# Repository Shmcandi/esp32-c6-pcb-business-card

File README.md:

# ESP32-C6 Smart PCB Business Card

An ultra-slim, monolithic smart electronic business card in the standard ISO/IEC 7810 ID-1 credit card form factor ($85.6 \times 54.0\text{ mm}$), powered by an **Espressif ESP32-C6-MINI-1** with an integrated **0.91" 128×32 SPI OLED display**, onboard USB-C programming and autonomous Li-Po battery charging.

Everything is designed for direct surface-mount soldering with **zero pin headers, zero sockets, and zero through-holes** for the OLED.

---

## 📸 Photorealistic 3D Renders

| Isometric / Perspective View | Top View | Bottom View |
| :---: | :---: | :---: |
|  |  |  |

---

## ⚡ Key Specifications

- **Dimensions:** $85.6\text{ mm} \times 54.0\text{ mm} \times 1.6\text{ mm}$ (Standard ID-1 Credit Card Size, $3.18\text{ mm}$ corner radius)
- **Microcontroller:** **ESP32-C6-MINI-1-N4**
  - High-performance 32-bit RISC-V processor (up to 160 MHz) + Low-power RISC-V coprocessor
  - 2.4 GHz Wi-Fi 6 (802.11ax), Bluetooth 5 (LE), Zigbee 3.0 & Thread (802.15.4 / Matter)
  - Onboard PCB trace antenna with dedicated RF clearance keepout
- **Display:** **0.91" 128×32 SPI OLED Display** (SSD1306 driver)
  - Direct SMD soldered via 6 castellated ENIG edge pads ($2.54\text{ mm}$ pitch)
  - **Zero through-holes / zero pin headers** — sits completely flush on the front copper
- **USB-C Interface:** GCT USB4105 16-pin USB Type-C receptacle
  - Native USB-Serial/JTAG for flashing firmware and serial debugging
  - $5.1\text{ k}\Omega$ CC pull-down resistors for USB-C PD compatibility
  - Powers and recharges the card from any standard USB-C port
- **Battery & Power System:**
  - Autonomous Li-Po charger: Microchip **MCP73831T-2ACI/OT** (configured for $\sim 300\text{ mA}$ charge rate)
  - Red SMD charge indicator LED (`CHG`)
  - Low-dropout regulator: Diodes Inc **AP2112K-3.3** ($600\text{ mA}$ output, $55\,\mu\text{A}$ quiescent current)
  - Battery connector: SMD horizontal JST-PH 2-pin connector (`J2`) + dedicated rear $30 \times 25\text{ mm}$ mounting area for adhesive-backed $3.7\text{V}$ Li-Po pouch cells (`302030` / `402030`, $150\text{–}250\text{ mAh}$)
- **Interactive Controls:**
  - `EN` (Reset) tactile switch (`SW1`) with RC debounce filter
  - `BOOT` (GPIO9) tactile switch (`SW2`) for firmware downloads / user input
  - `USER` (GPIO4) tactile switch (`SW3`) for custom menu / interaction

---

## 📌 ESP32-C6 Pinout & Signal Mapping

| Signal | ESP32-C6 Pin | GPIO / Function | Description |
| :--- | :---: | :---: | :--- |
| **OLED SCL / SCK** | Pin 19 | GPIO14 | SPI Clock |
| **OLED SDA / MOSI**| Pin 20 | GPIO15 | SPI Master Out Slave In |
| **OLED RES** | Pin 22 | GPIO8 | Display Hardware Reset |
| **OLED DC** | Pin 24 | GPIO18 | Data / Command Selection |
| **USER Button** | Pin 9 | GPIO4 | Active-Low User Input Button |
| **BOOT Button** | Pin 23 | GPIO9 | Boot Mode / User Button 2 |
| **RESET Button** | Pin 8 | CHIP_EN | Chip Enable / Reset |
| **USB D-** | Pin 17 | GPIO12 | Native USB Serial/JTAG D- |
| **USB D+** | Pin 18 | GPIO13 | Native USB Serial/JTAG D+ |
| **STAT** | — | — | MCP73831 Charger Status to LED `D1` |

---

## 📦 Manufacturing & Ordering Files

The card is 100% routed and DRC verified in KiCad:
- **Gerbers & Drill Package:** [`aio_card_gerbers.zip`](aio_card_gerbers.zip) — Ready for one-click upload to JLCPCB / PCBWay / Oshpark.
- **Full KiCad PCB:** [`aio_card.kicad_pcb`](aio_card.kicad_pcb)
- **Bill of Materials (BOM):** [`fab_aio/BOM.csv`](fab_aio/BOM.csv)
- **Pick-and-Place Centroids (CPL):** [`fab_aio/CPL.csv`](fab_aio/CPL.csv)
- **Design Automation Script:** [`c6_card.py`](c6_card.py)

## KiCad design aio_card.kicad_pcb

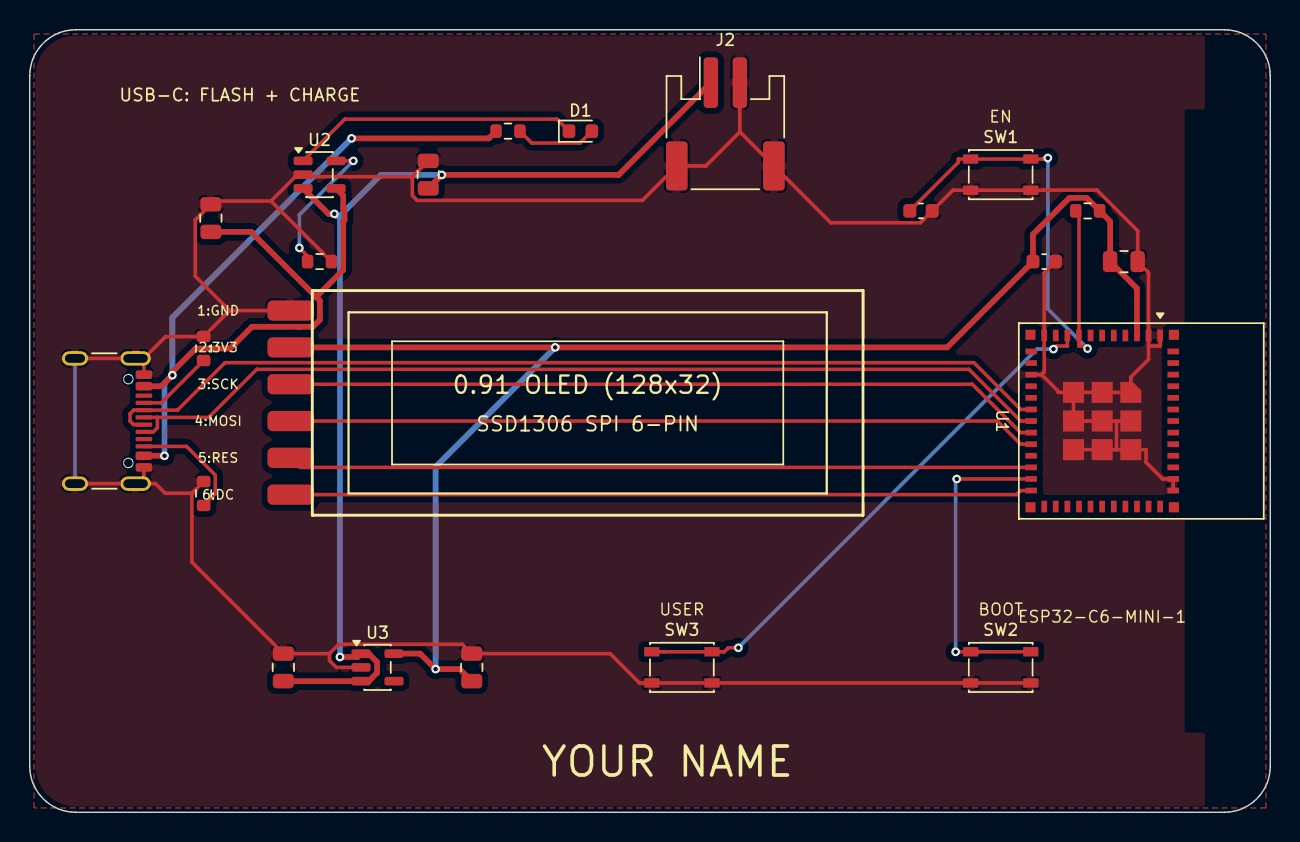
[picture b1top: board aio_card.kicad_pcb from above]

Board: 2 copper layers, 85.6 x 54.0 mm, 22 parts (0 on the bottom side), 18 nets.

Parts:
C1, C2: 4.7uF; C_0805_2012Metric
C3, C4, C6: 10uF; C_0805_2012Metric
C5: 100nF; C_0603_1608Metric
C7: 1uF; C_0603_1608Metric
D1: CHG; LED_0603_1608Metric
J1: USB-C (USB4105); USB_C_Receptacle_GCT_USB4105-xx-A_16P_TopMnt_Horizontal
J2: BATT JST-PH; JST_PH_S2B-PH-SM4-TB_1x02-1MP_P2.00mm_Horizontal
J3: 0.91" OLED (SPI); OLED_6PIN_SMD
R1, R2: 5.1k; R_0603_1608Metric
R3: 3.3k; R_0603_1608Metric
R4: 10k; R_0603_1608Metric
R6: 1k; R_0603_1608Metric
SW1: EN; SW_SPST_PTS810
SW2: BOOT; SW_SPST_PTS810
SW3: USER; SW_SPST_PTS810
U1: ESP32-C6-MINI-1-N4; ESP32-C6-MINI-1
U2: MCP73831T-2ACI/OT; SOT-23-5
U3: AP2112K-3.3; SOT-23-5

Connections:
3V3: C4.1, C5.1, C6.1, J3.2, R4.2, U1.3, U3.5
BOOT: SW2.1, U1.23
BTN: SW3.1, U1.9
CC1: J1.A5, R1.1
CC2: J1.B5, R2.1
DC: J3.6, U1.24
EN: C7.1, R4.1, SW1.1, U1.8
GND: C1.2, C2.2, C3.2, C4.2, C5.2, C6.2, C7.2, J1.A1, J1.A12, J1.B1, J1.B12, J1.SH, J2.2, J2.MP, J3.1, R1.2, R2.2, R3.2, SW1.2, SW2.2, SW3.2, U1.1, U1.2, U1.11, U1.14, U1.36, U1.37, U1.49, U2.2, U3.2
LEDA: D1.2, R6.2
MOSI: J3.4, U1.20
PROG: R3.1, U2.5
RES: J3.5, U1.22
SCK: J3.3, U1.19
STAT: D1.1, U2.1
USB_DN: J1.A7, J1.B7, U1.17
USB_DP: J1.A6, J1.B6, U1.18
VBAT: C2.1, C3.1, J2.1, U2.3, U3.1, U3.3
VBUS: C1.1, J1.A4, J1.A9, J1.B4, J1.B9, R6.1, U2.4

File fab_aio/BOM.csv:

Comment,Designator,Footprint,Part (search this on LCSC / JLCPCB)
ESP32-C6-MINI-1-N4,U1,ESP32-C6-MINI-1,Espressif ESP32-C6-MINI-1-N4 (or N8)
USB-C receptacle,J1,USB4105 16P horizontal,GCT USB4105-GF-A
MCP73831T-2ACI/OT,U2,SOT-23-5,Microchip MCP73831T-2ACI/OT (4.2V LiPo charger)
AP2112K-3.3,U3,SOT-23-5,Diodes AP2112K-3.3TRG1 (3.3V 600mA LDO)
5.1k,"R1,R2",0603,5.1k 1% (USB-C CC pull-downs)
3.3k,R3,0603,3.3k 1% (charge current ~300mA)
10k,R4,0603,10k 1%
1k,R6,0603,1k 1%
4.7uF,"C1,C2",0805,4.7uF 10V X5R
10uF,"C3,C4,C6",0805,10uF 10V X5R
100nF,C5,0603,100nF 16V X7R
1uF,C7,0603,1uF 16V X7R
LED red,D1,0603,Red LED 0603
Tact switch,"SW1,SW2,SW3",PTS810,C&K PTS810 SJM 250 SMTR LFS (or equivalent)
JST PH 2-pin SMD,J2,S2B-PH-SM4-TB,JST S2B-PH-SM4-TB
0.91" 128x32 SPI OLED Display Module (SSD1306),J3,OLED_6PIN_SMD,Direct Surface-Mount Soldered (Castellated SMD pads / No pin headers)

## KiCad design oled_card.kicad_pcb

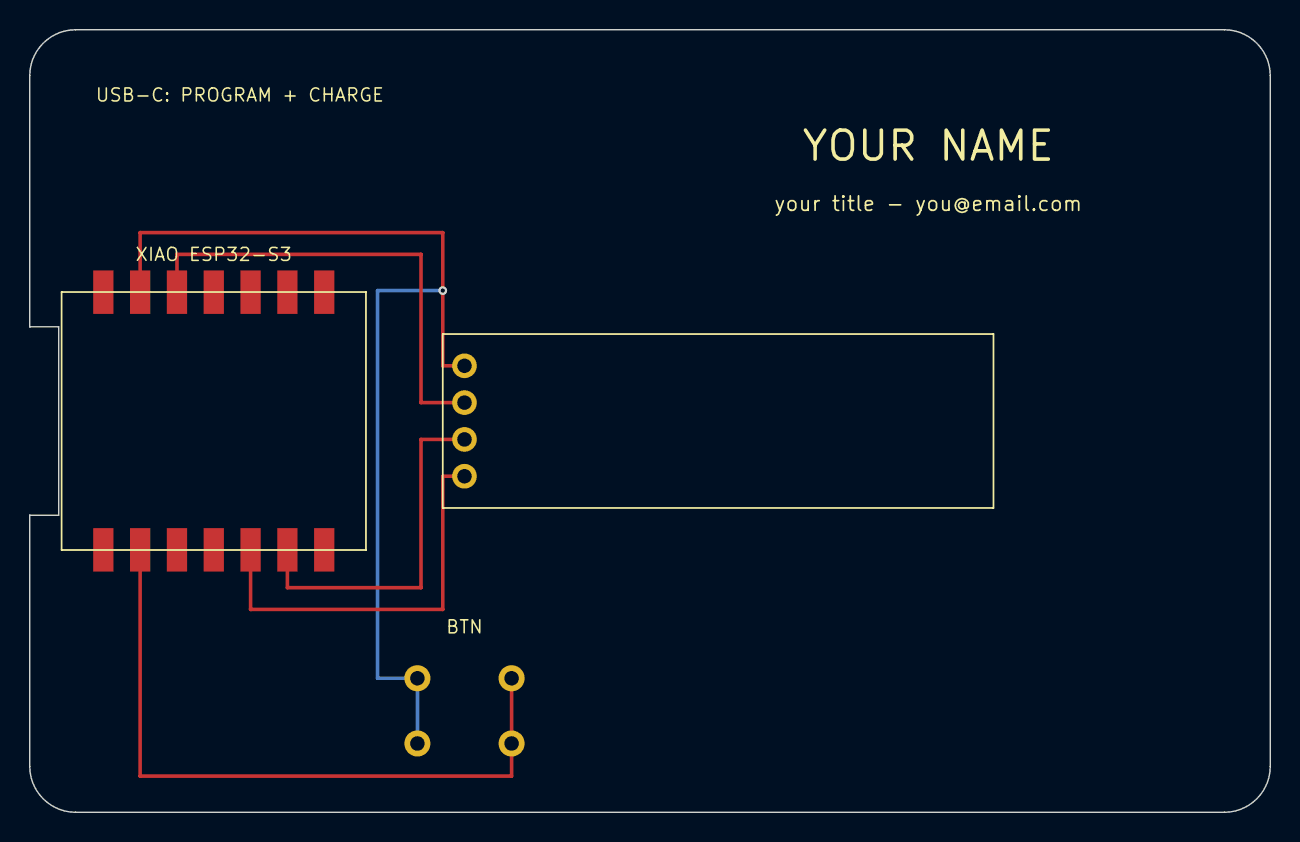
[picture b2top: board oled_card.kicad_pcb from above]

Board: 2 copper layers, 85.6 x 54.0 mm, 3 parts (0 on the bottom side), 5 nets.

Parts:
J1: OLED_0.91_I2C; J1_OLED_0.91_I2C
SW1: TACT_6x6; SW1_TACT_6x6
U1: XIAO_ESP32S3; U1_XIAO_ESP32S3

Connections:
3V3: J1.2, U1.12
BTN: SW1.3, SW1.4, U1.2
GND: J1.1, SW1.1, SW1.2, U1.13
SCL: J1.3, U1.6
SDA: J1.4, U1.5

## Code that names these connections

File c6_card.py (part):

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# Pin 8 -> EN
# Pin 23 -> IO9 (BOOT button on ESP32-C6!)
# Pin 9 -> IO4 (USER button)
# Pin 17 -> IO12 (USB_DN)
# Pin 18 -> IO13 (USB_DP)
# Pin 19 -> IO14 (OLED SCL / SCK)
# Pin 20 -> IO15 (OLED SDA / MOSI)
# Pin 22 -> IO8 (OLED RES)
# Pin 24 -> IO18 (OLED DC)

PARTS = [
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    out += text_sexpr("SSD1306 SPI 6-PIN", 38.5, 27.2, 1.0, 0.13)

    # 5. Clear pin labels for the 6 direct-solder pads
    pins = ["1:GND", "2:3V3", "3:SCK", "4:MOSI", "5:RES", "6:DC"]
    for i, p in enumerate(pins):
        y = 19.38 + i * 2.54
        out += text_sexpr(p, 13.0, y, 0.65, 0.10)
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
